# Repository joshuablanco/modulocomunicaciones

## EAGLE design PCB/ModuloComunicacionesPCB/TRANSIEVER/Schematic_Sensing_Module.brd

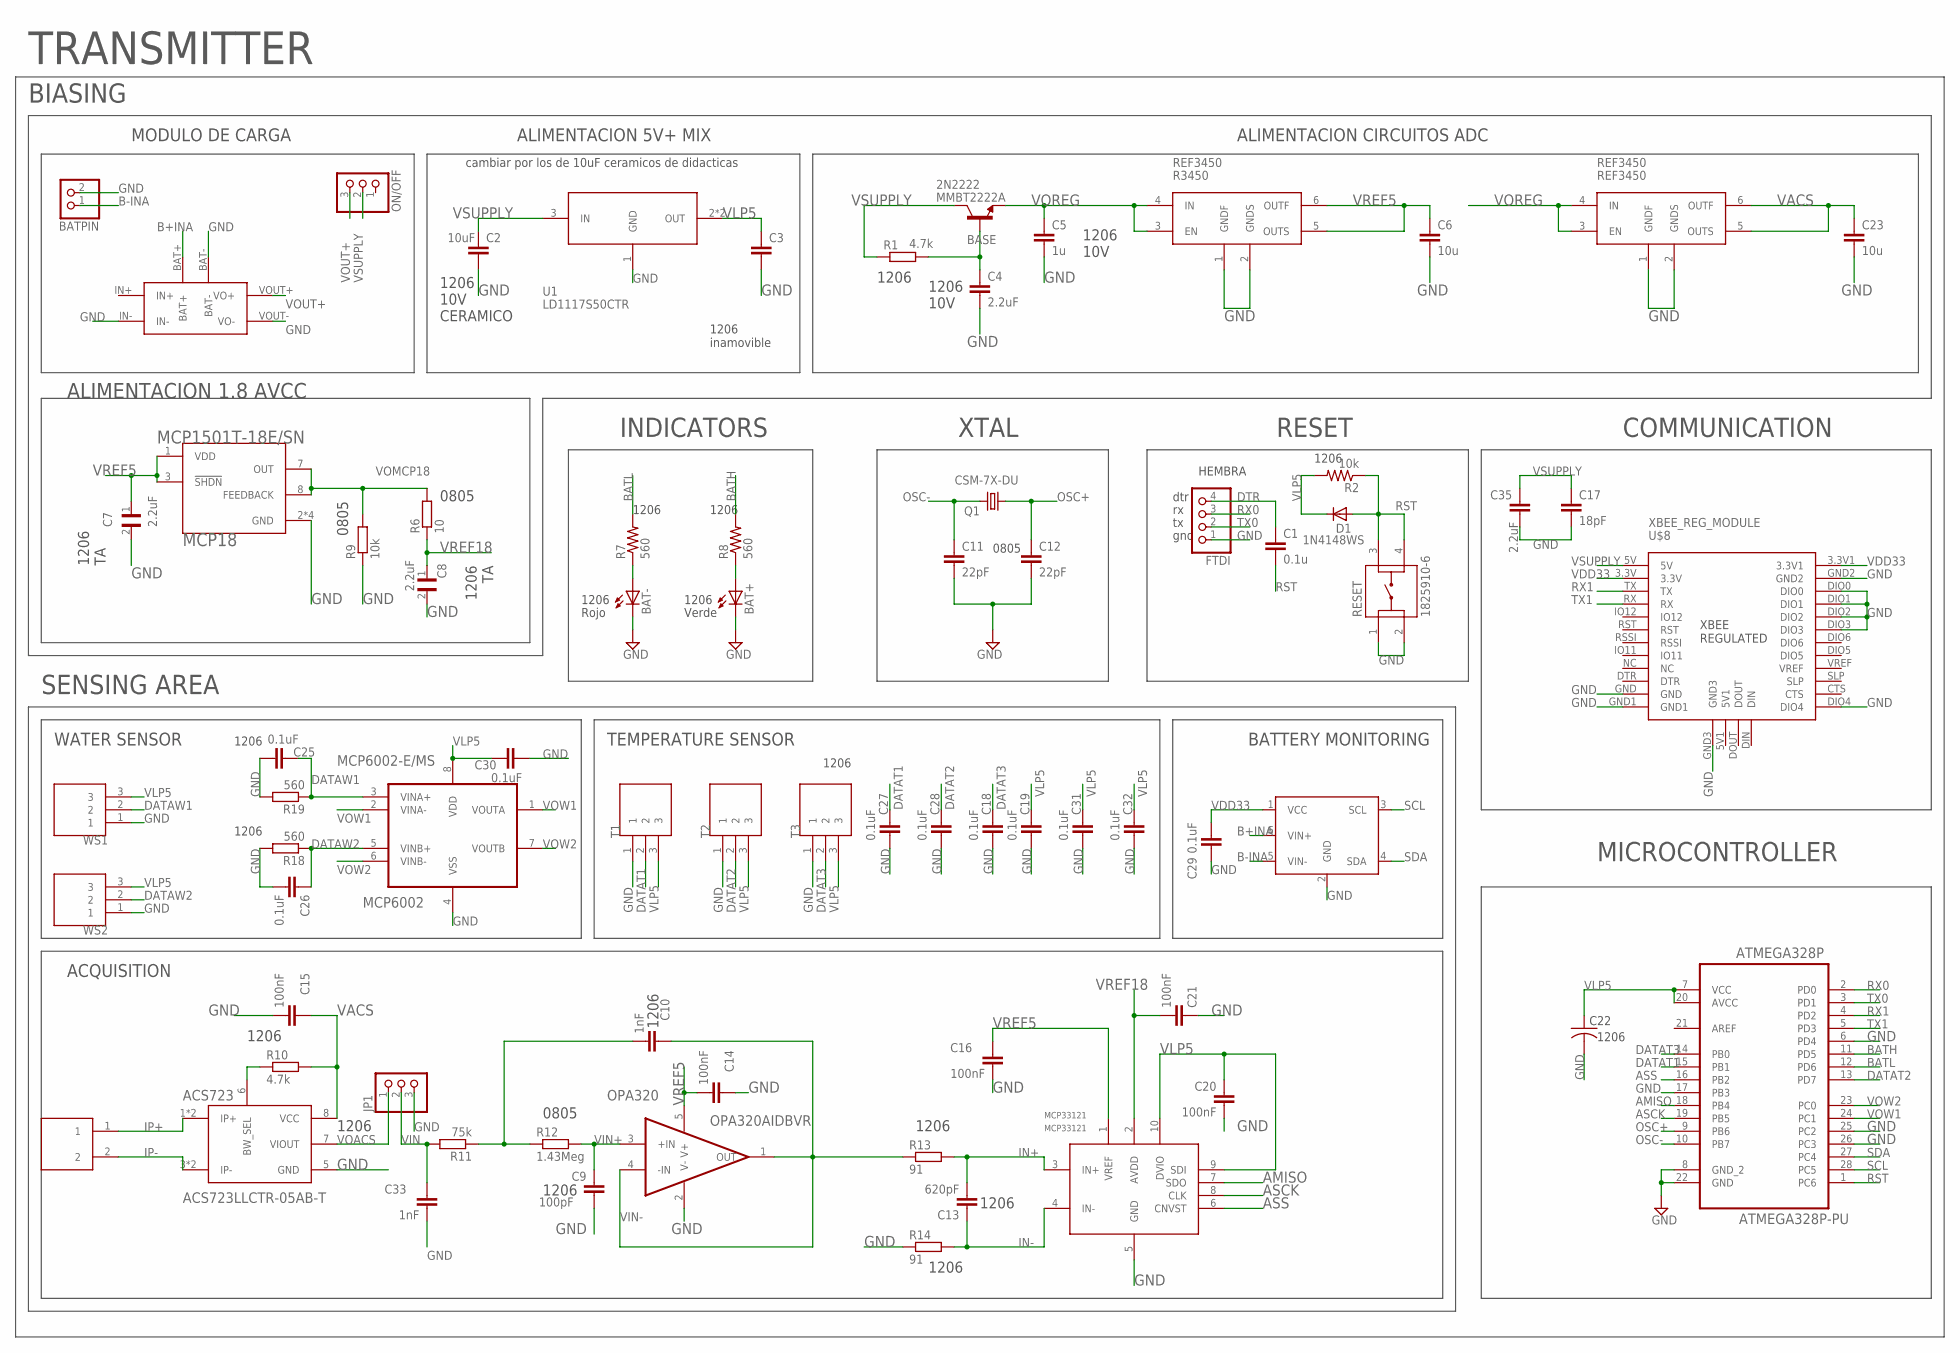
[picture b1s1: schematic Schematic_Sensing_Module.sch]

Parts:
2N2222: MMBT2222A; SOT23
ACS723: ACS723LLCTR-05AB-T; SOIC127P600X175-8N
ATMEGA328P: ATMEGA328P-PU; DIP254P762X457-28
BAT+: LEDCHIPLED_1206; CHIPLED_1206
BAT-: LEDCHIPLED_1206; CHIPLED_1206
BATPIN: PINHD-1X2; 1X02
C1: 0.1u; C0805
C2, C3: 10uF; C1206
C4, C35: 2.2uF; C1206
C5: 1u; C1206
C6, C23: 10u; C1206
C7, C8: 2.2uF; CAPC3216X110N
C9: 100pF; C1206
C10, C33: 1nF; C1206
C11, C12: 22pF; C0805
C13: 620pF; C1206
C14, C15, C16, C20, C21: 100nF; C1206
C17: 18pF; C0805
C18, C19, C22, C25, C26, C27, C28, C29, C30, C31, C32: 0.1uF; C1206
D1: 1N4148WS; SOD323
FTDI: PINHD-1X4; 1X04
IACT: TERMINAL-TB2
INA219: INABB; INA219-MODULE
JP1: PINHD-1X3; 1X03
MCP18: MCP1501T-18E/SN; SOIC127P600X175-8N
MCP6002: MCP6002-E/MS; SOP65P490X110-8N
MCP33121: MCP33121; MSOP10
ON/OFF: PINHD-1X3; 1X03
OPA320: OPA320AIDBVR; SOT95P280X145-5N
POWER-SUPP: MODULO_CARGA_DEVICE; MODULO_CARGA
Q1: CSM-7X-DU
R1: 4.7k; R1206
R2: 10k; R1206
R6: 10; R0805
R7, R8, R18, R19: 560; R1206
R9: 10k; R0805
R10: 4.7k; M1206
R11: 75k; R1206
R12: 1.43Meg; R0805
R13, R14: 91; R1206
R3450: REF3450; SOT95P280X145-6N
REF3450: REF3450; SOT95P280X145-6N
RESET: 1825910-6; SW_1825910-6-4
T1, T2, T3: TERMINAL-TB3
U1: LD1117S50CTR; SOT223
U$8: XBEE_REG_MODULE; XBEE_REG
WS1, WS2: TERMINAL-TB3

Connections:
AMISO: ATMEGA328P.18 (PB4), MCP33121.7 (SDO)
ASCK: ATMEGA328P.19 (PB5), MCP33121.8 (CLK)
ASS: ATMEGA328P.16 (PB2), MCP33121.6 (CNVST)
B+INA: INA219.6 (VIN+), POWER-SUPP.BAT+
B-INA: BATPIN.1, INA219.5 (VIN-)
BASE: 2N2222.1 (B), C4.1, R1.2
BATH: ATMEGA328P.11 (PD5), R8.2
BATL: ATMEGA328P.12 (PD6), R7.2
BWSEL: ACS723.6 (BW_SEL), R10.1
DATAT1: ATMEGA328P.15 (PB1), C27.1, T1.2
DATAT2: ATMEGA328P.13 (PD7), C28.1, T2.2
DATAT3: ATMEGA328P.14 (PB0), C18.1, T3.2
DATAW1: C25.1, MCP6002.3 (VINA+), R19.1, WS1.2
DATAW2: C26.1, MCP6002.5 (VINB+), R18.1, WS2.2
DTR: C1.1, FTDI.4
GND: ACS723.5 (GND), ATMEGA328P.6 (PD4), ATMEGA328P.8 (GND_2), ATMEGA328P.17 (PB3), ATMEGA328P.22 (GND), ATMEGA328P.25 (PC2), ATMEGA328P.26 (PC3), BAT+.C, BAT-.C, BATPIN.2, C2.2, C3.2, C4.2, C5.2, C6.2, C7.2, C8.2, C9.2, C11.2, C12.2, C14.1, C15.2, C16.2, C17.2, C18.2, C19.2, C20.2, C21.1, C22.2, C23.2, C25.2, C26.2, C27.2, C28.2, C29.2, C30.2, C31.2, C32.2, C33.2, C35.2, FTDI.1, INA219.2 (GND), JP1.3, MCP18.2 (GND), MCP18.4 (GND), MCP18.5 (GND), MCP18.6 (GND), MCP6002.4 (VSS), MCP33121.5 (GND), OPA320.2 (V-), POWER-SUPP.BAT-, POWER-SUPP.IN-, POWER-SUPP.VOUT- (VO-), R9.1, R14.1, R18.2, R19.2, R3450.1 (GNDF), R3450.2 (GNDS), REF3450.1 (GNDF), REF3450.2 (GNDS), RESET.1, RESET.2, T1.1, T2.1, T3.1, U1.1 (GND), U$8.DIO0, U$8.DIO1, U$8.DIO2, U$8.DIO3, U$8.DIO4, U$8.GND, U$8.GND1, U$8.GND2, U$8.GND3, WS1.1, WS2.1
IN+: C13.2, MCP33121.3 (IN+), R13.2
IN-: C13.1, MCP33121.4 (IN-), R14.2
IP+: ACS723.1 (IP+), ACS723.2 (IP+), IACT.1
IP-: ACS723.3 (IP-), ACS723.4 (IP-), IACT.2
unnamed: BAT-.A, R7.1
unnamed: BAT+.A, R8.1
unnamed: C10.2, R11.1, R12.1
OSC+: ATMEGA328P.9 (PB6), C12.1, Q1.1
OSC-: ATMEGA328P.10 (PB7), C11.1, Q1.2
RST: ATMEGA328P.1 (PC6), C1.2, D1.A, R2.1, RESET.3, RESET.4
RX0: ATMEGA328P.2 (PD0), FTDI.3
RX1: ATMEGA328P.4 (PD2), U$8.TX
SCL: ATMEGA328P.28 (PC5), INA219.3 (SCL)
SDA: ATMEGA328P.27 (PC4), INA219.4 (SDA)
TX0: ATMEGA328P.3 (PD1), FTDI.2
TX1: ATMEGA328P.5 (PD3), U$8.RX
VACS: ACS723.8 (VCC), C15.1, C23.1, R10.2, REF3450.5 (OUTS), REF3450.6 (OUTF)
VDD33: C29.1, INA219.1 (VCC), U$8.3.3V, U$8.3.3V1
VIN: C33.1, JP1.2, R11.2
VIN+: C9.1, OPA320.3 (+IN), R12.2
VIN-: C10.1, OPA320.1 (OUT), OPA320.4 (-IN), R13.1
VLP5: ATMEGA328P.7 (VCC), ATMEGA328P.20 (AVCC), C3.1, C19.1, C20.1, C22.1, C30.1, C31.1, C32.1, D1.C, MCP6002.8 (VDD), MCP33121.9 (SDI), MCP33121.10 (DVIO), R2.2, T1.3, T2.3, T3.3, U1.2 (OUT), U1.4 (OUT), WS1.3, WS2.3
VOACS: ACS723.7 (VIOUT), JP1.1
VOMCP18: MCP18.7 (OUT), MCP18.8 (FEEDBACK), R6.2, R9.2
VOREG: 2N2222.2 (E), C5.1, R3450.3 (EN), R3450.4 (IN), REF3450.3 (EN), REF3450.4 (IN)
VOUT+: ON/OFF.3, POWER-SUPP.VOUT+ (VO+)
VOW1: ATMEGA328P.24 (PC1), MCP6002.1 (VOUTA), MCP6002.2 (VINA-)
VOW2: ATMEGA328P.23 (PC0), MCP6002.6 (VINB-), MCP6002.7 (VOUTB)
VREF5: C6.1, C7.1, C14.2, C16.1, MCP18.1 (VDD), MCP18.3 (!SHDN), MCP33121.1 (VREF), OPA320.5 (V+), R3450.5 (OUTS), R3450.6 (OUTF)
VREF18: C8.1, C21.2, MCP33121.2 (AVDD), R6.1
VSUPPLY: 2N2222.3 (C), C2.1, C17.1, C35.1, ON/OFF.2, R1.1, U1.3 (IN), U$8.5V

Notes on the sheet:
XTAL
TEMPERATURE SENSOR
WATER SENSOR
RESET
INDICATORS
TRANSMITTER
BATTERY MONITORING
SENSING AREA
BIASING
1206
COMMUNICATION
MICROCONTROLLER
ACQUISITION
Rojo
Verde
HEMBRA
dtr
gnd
MODULO DE CARGA
1206 10V CERAMICO
1206 10V
ALIMENTACION 5V+ MIX
ALIMENTACION CIRCUITOS ADC
0805
1206 TA
ALIMENTACION 1.8 AVCC
1206 inamovible
cambiar por los de 10uF ceramicos de didacticas

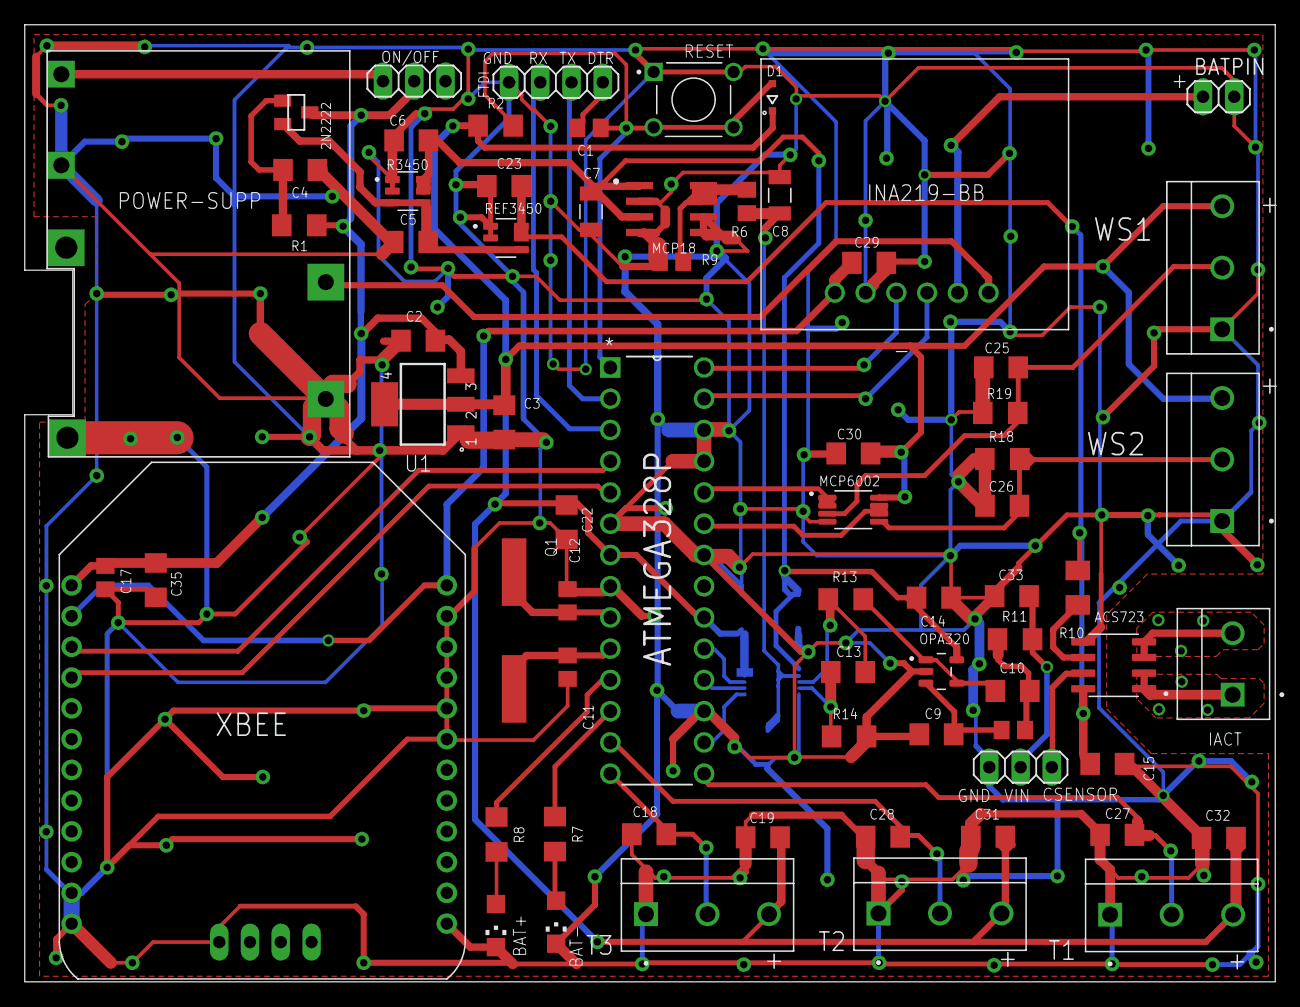
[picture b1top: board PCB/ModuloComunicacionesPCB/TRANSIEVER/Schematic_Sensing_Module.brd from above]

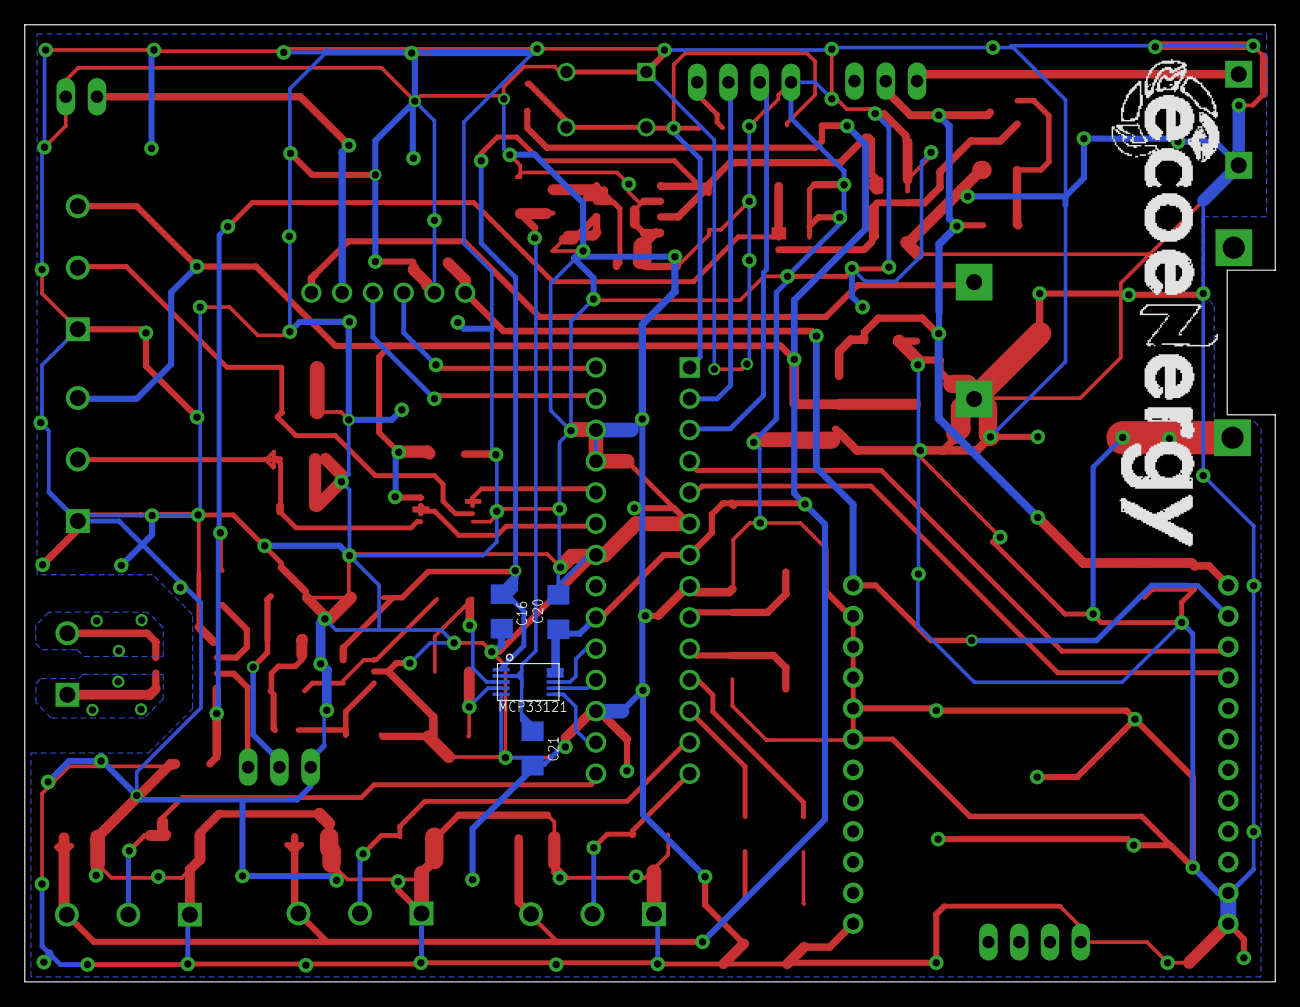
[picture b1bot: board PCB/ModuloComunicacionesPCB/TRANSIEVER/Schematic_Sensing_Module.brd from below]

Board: 2 copper layers, 101.7 x 77.8 mm, 74 parts (4 on the bottom side), 47 nets.

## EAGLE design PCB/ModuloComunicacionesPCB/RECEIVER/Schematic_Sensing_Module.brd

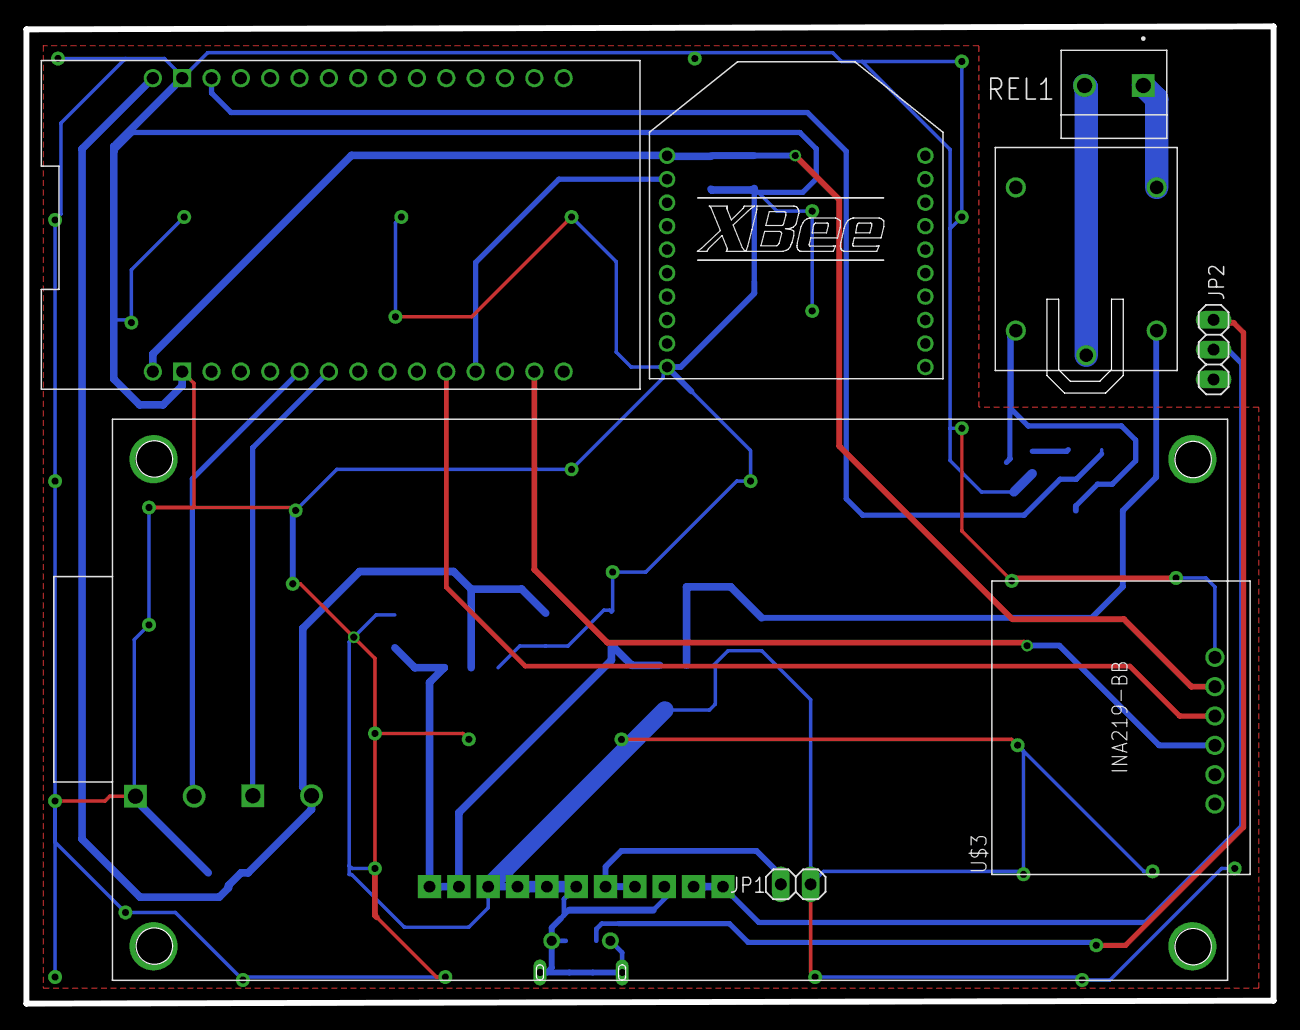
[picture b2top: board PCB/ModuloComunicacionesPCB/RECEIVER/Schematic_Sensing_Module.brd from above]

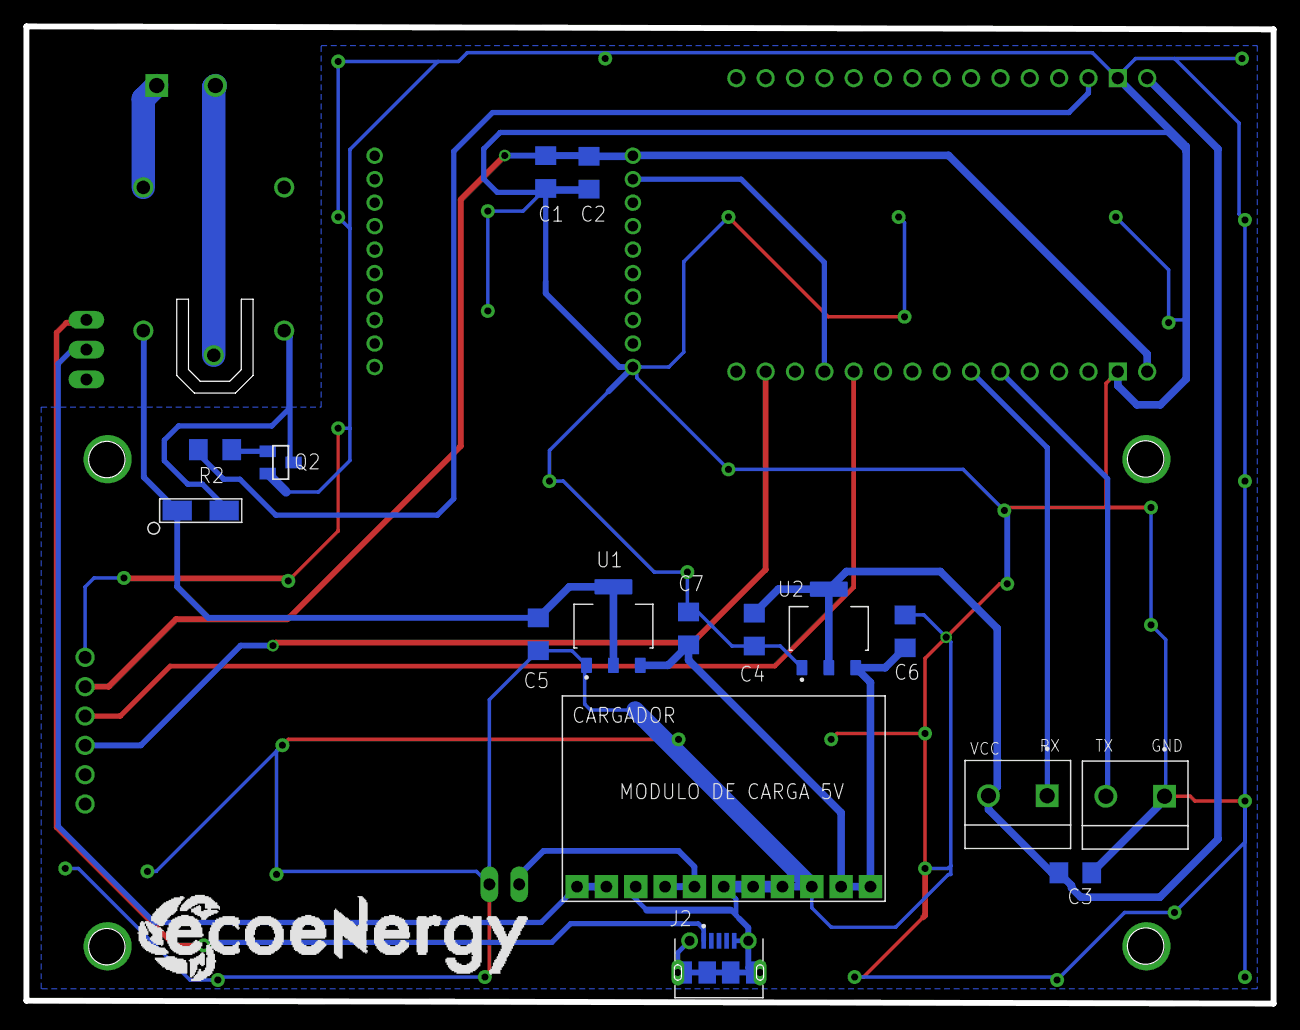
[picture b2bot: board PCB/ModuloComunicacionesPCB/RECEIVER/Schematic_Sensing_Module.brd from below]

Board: 2 copper layers, 106.2 x 83.2 mm, 24 parts (16 on the bottom side), 18 nets.

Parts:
1N4007: 1N4007SMA; SMA
C1, C3: 100nF; C1206
C2: 1u; C1206
C4, C5, C6, C7: C1206
CARGADOR: MODULO_CARGA_5V
CONN1, CONN2: TERMINAL-TB2
J2: 1050170001; MOLEX_1050170001
JP1: 1X02
JP2: 1X03
Q2: MMBT2222A; SOT23
R2: 10k; R1206
REL1: TERMINAL-TB2
U1, U2: AMS1117-5.0; SOT229P700X180-4N
U$1: ESP32-W; DIP
U$2: NX4024T032
U$3: INABB; INA219-MODULE
U$5: SRD-3; SRD-N
U$9: XBEE-S2C; XBEE-DIP

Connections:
CR1: REL1.2, U$5.C
DOUT: U$1.RX0, U$9.2
GND: C1.2, C2.1, C3.2, C4.2, C5.2, C6.2, C7.2, CARGADOR.GND, CARGADOR.GND1, CARGADOR.GND2, CARGADOR.GND3, CARGADOR.GND4, CONN1.1, J2.5, J2.SH1, J2.SH2, J2.SH3, J2.SH4, J2.SH5, J2.SH6, J2.SH7, J2.SH8, JP1.2, Q2.2, U1.1, U2.1, U$1.GND, U$1.GND1, U$3.6, U$9.10
unnamed: Q2.1, R2.2
unnamed: 1N4007.1, Q2.3, U$5.VL-
NOR1: REL1.1, U$5.NO
RXNEX: CONN2.1, U$1.TX2
SCL: U$1.D22, U$3.3
SDA: U$1.D21, U$3.4
TXNEX: CONN1.2, U$1.RX2
VBAT: CARGADOR.BAT, CARGADOR.BAT1, JP1.1
VDEVICES: C3.1, C4.1, CONN2.2, U2.2, U2.4, U$1.VIN
VINCHAR: J2.1, JP2.1
VON: CARGADOR.VIN, CARGADOR.VIN1, JP2.2
VOUTCH: C6.1, C7.1, CARGADOR.VOUT, CARGADOR.VOUT1, U1.3, U2.3
VOUTRELAYS: 1N4007.2, C5.1, U1.2, U1.4, U$5.VL+
VR1: R2.1, U$1.D13
VXBEE: C1.1, C2.2, U$1.3V3, U$3.5, U$9.1

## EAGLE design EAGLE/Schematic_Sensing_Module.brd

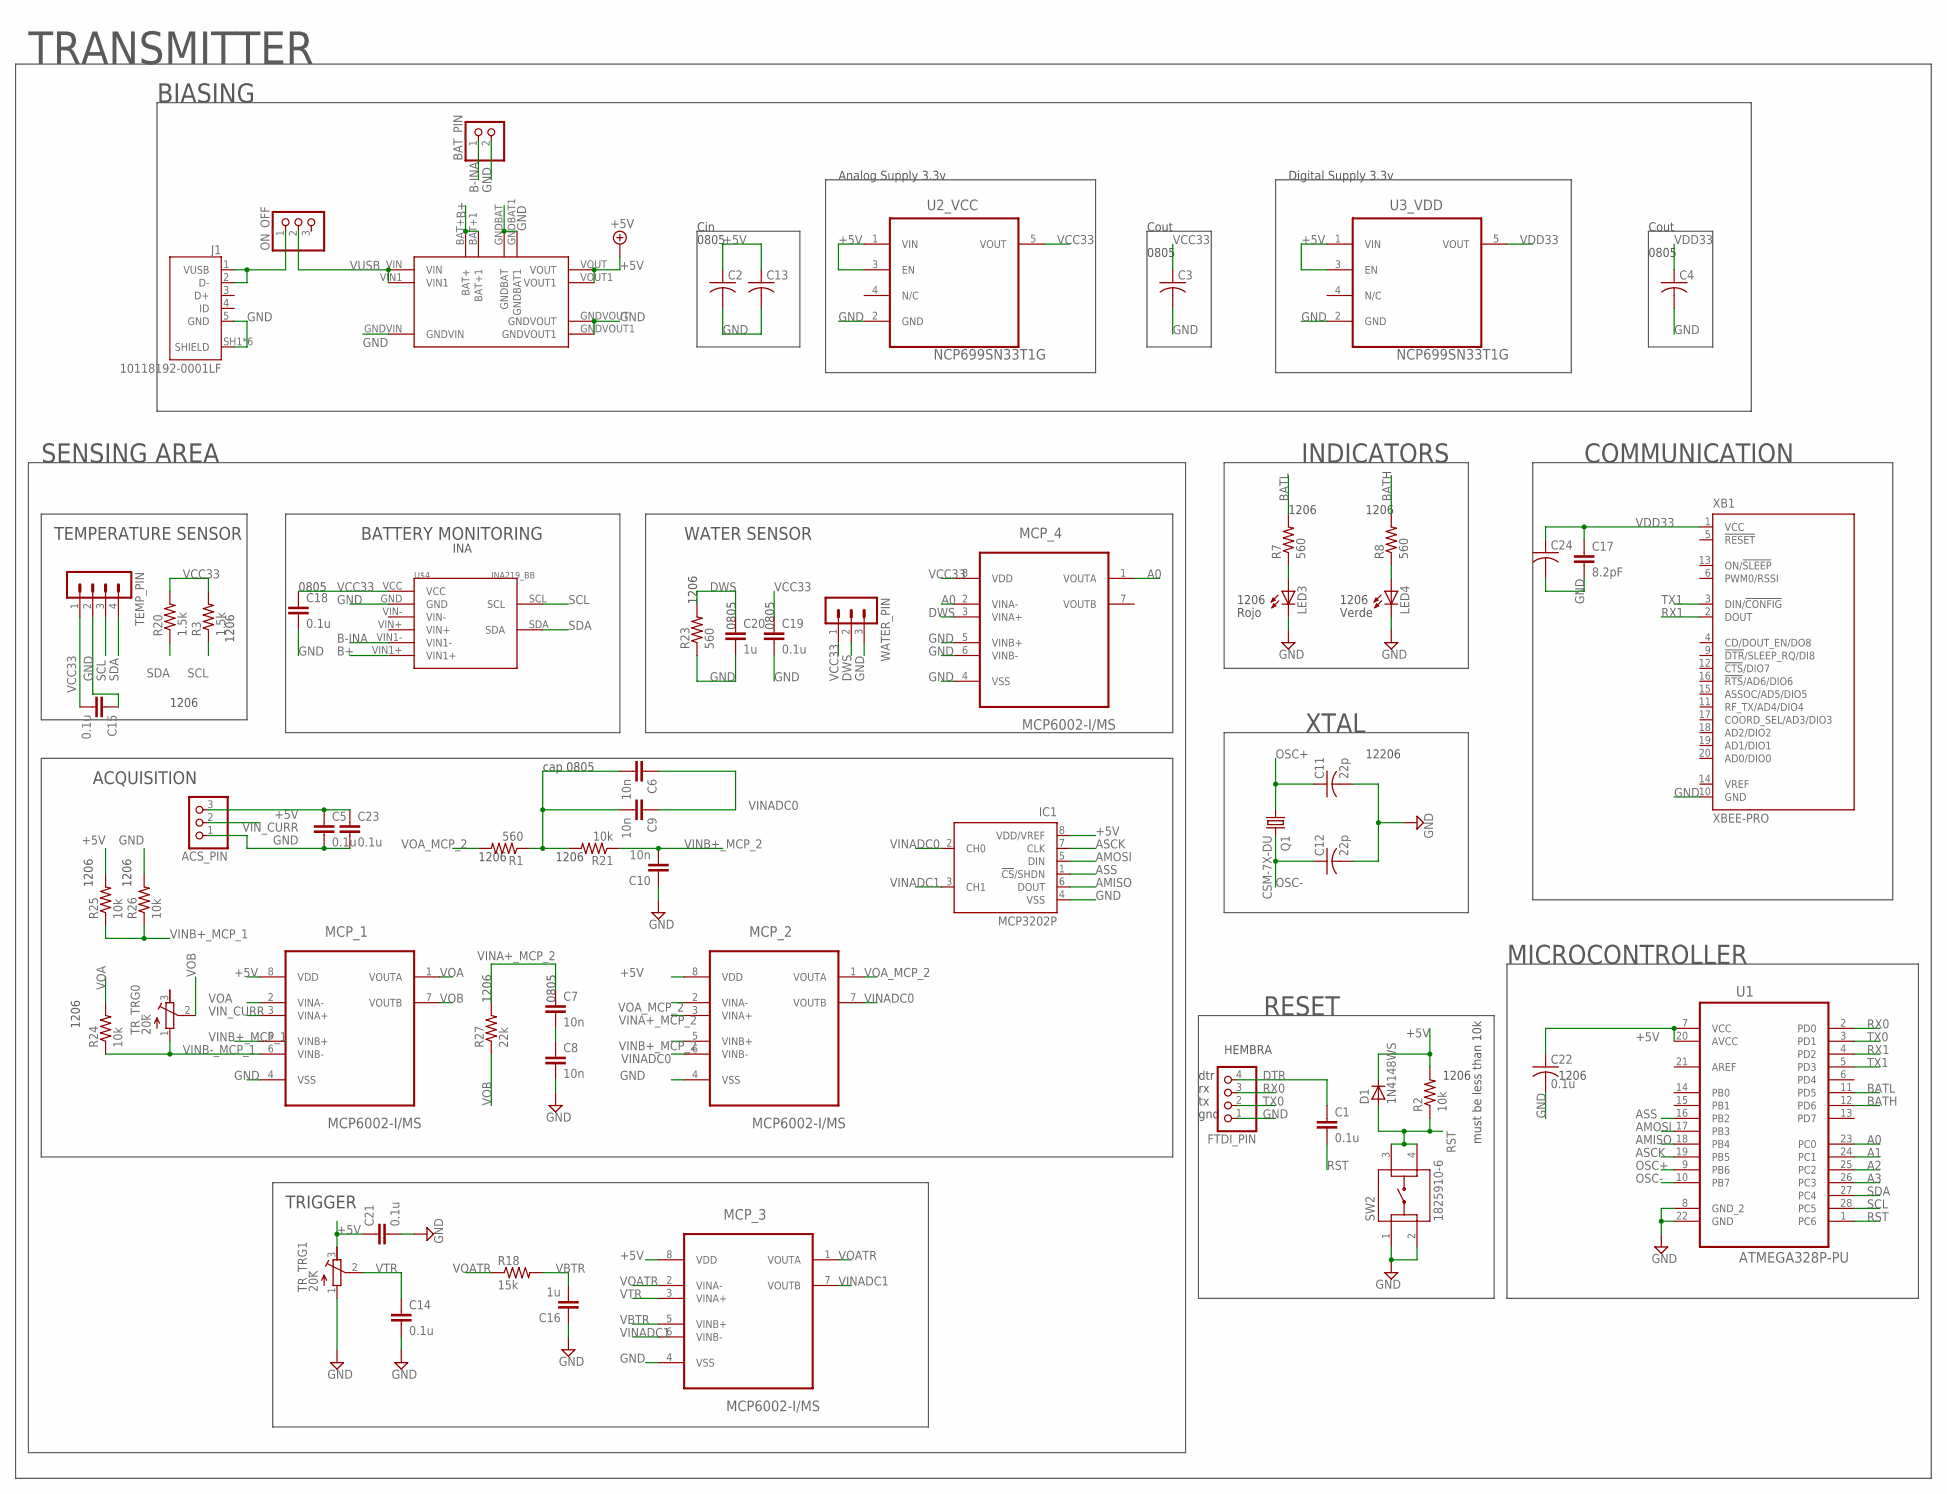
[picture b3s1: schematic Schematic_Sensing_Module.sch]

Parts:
ACS_PIN: PINHD-1X3; 1X03
BAT_PIN: PINHD-1X2; 1X02
C1, C5, C14, C15, C18, C19, C21, C23: 0.1u; C0805
C2, C3, C4, C13, C24: C-USC0805; C0805
C6, C7, C8, C9, C10: 10n; C0805
C11, C12: 22p; C1206
C16, C20: 1u; C0805
C17: 8.2pF; C0805
C22: 0.1u; C1206
D1: 1N4148WS; SOD323
FTDI_PIN: PINHD-1X4; 1X04
IC1: MCP3202P; DIL8
J1: 10118192-0001LF; AMPHENOL_10118192-0001LF
LED3, LED4: LEDCHIPLED_1206; CHIPLED_1206
MCP_1, MCP_2, MCP_3, MCP_4: MCP6002-I/MS; SOP65P490X110-8N
ON_OFF: PINHD-1X3; 1X03
Q1: CSM-7X-DU
R1, R7, R8, R23: 560; R1206
R2, R21, R24, R25, R26: 10k; R1206
R3, R20: 1.5k; R1206
R18: 15k; R0805
R27: 22k; R1206
SW2: 1825910-6; SW_1825910-6-4
TEMP_PIN: MA04-1
TR_TRG0: 20k; RTRIM64W
TR_TRG1: 20K; RTRIM64W
U1: ATMEGA328P-PU; DIP254P762X457-28
U2_VCC, U3_VDD: NCP699SN33T1G; SOT95P275X110-5N
U$2: UPS-LIPO
U$4: INA219_BB
WATER_PIN: MA03-1
XB1: XBEE-PRO

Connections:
+5V: ACS_PIN.3, C2.1, C5.1, C13.1, C21.1, C22.1, C23.1, D1.C, IC1.8 (VDD/VREF), MCP_1.8 (VDD), MCP_2.8 (VDD), MCP_3.8 (VDD), R2.2, R25.2, TR_TRG1.3 (E), U1.7 (VCC), U1.20 (AVCC), U2_VCC.1 (VIN), U2_VCC.3 (EN), U3_VDD.1 (VIN), U3_VDD.3 (EN), U$2.VOUT, U$2.VOUT1
A0: MCP_4.1 (VOUTA), MCP_4.2 (VINA-), U1.23 (PC0)
A1: U1.24 (PC1)
A2: U1.25 (PC2)
A3: U1.26 (PC3)
AMISO: IC1.6 (DOUT), U1.18 (PB4)
AMOSI: IC1.5 (DIN), U1.17 (PB3)
ASCK: IC1.7 (CLK), U1.19 (PB5)
ASS: IC1.1 (!CS!/SHDN), U1.16 (PB2)
B+: U$2.BAT+, U$2.BAT+1, U$4.VIN1+
B-INA: BAT_PIN.1, U$4.VIN1-
BATH: R8.2, U1.12 (PD6)
BATL: R7.2, U1.11 (PD5)
DTR: C1.1, FTDI_PIN.4
DWS: C20.1, MCP_4.3 (VINA+), R23.2, WATER_PIN.2
GND: ACS_PIN.1, BAT_PIN.2, C2.2, C3.2, C4.2, C5.2, C8.2, C10.1, C11.2, C12.2, C13.2, C14.2, C15.1, C16.1, C17.2, C18.2, C19.2, C20.2, C21.2, C22.2, C23.2, C24.2, FTDI_PIN.1, IC1.4 (VSS), J1.5 (GND), J1.SH1 (SHIELD), J1.SH2 (SHIELD), J1.SH3 (SHIELD), J1.SH4 (SHIELD), J1.SH5 (SHIELD), J1.SH6 (SHIELD), LED3.C, LED4.C, MCP_1.4 (VSS), MCP_2.4 (VSS), MCP_3.4 (VSS), MCP_4.4 (VSS), MCP_4.5 (VINB+), MCP_4.6 (VINB-), R23.1, R26.2, SW2.1, SW2.2, TEMP_PIN.2, TR_TRG1.1 (A), U1.8 (GND_2), U1.22 (GND), U2_VCC.2 (GND), U3_VDD.2 (GND), U$2.GNDBAT, U$2.GNDBAT1, U$2.GNDVIN, U$2.GNDVOUT, U$2.GNDVOUT1, U$4.GND, WATER_PIN.3, XB1.10 (GND)
unnamed: J1.1 (VUSB), J1.2 (D-), ON_OFF.1
unnamed: LED3.A, R7.1
unnamed: LED4.A, R8.1
unnamed: C7.2, C8.1
unnamed: C6.2, C9.2, R1.1, R21.2
OSC+: C11.1, Q1.1, U1.9 (PB6)
OSC-: C12.1, Q1.2, U1.10 (PB7)
RST: C1.2, D1.A, R2.1, SW2.3, SW2.4, U1.1 (PC6)
RX0: FTDI_PIN.3, U1.2 (PD0)
RX1: U1.4 (PD2), XB1.2 (DOUT)
SCL: R3.1, TEMP_PIN.3, U1.28 (PC5), U$4.SCL
SDA: R20.1, TEMP_PIN.4, U1.27 (PC4), U$4.SDA
TX0: FTDI_PIN.2, U1.3 (PD1)
TX1: U1.5 (PD3), XB1.3 (DIN/!CONFIG)
VBTR: C16.2, MCP_3.5 (VINB+), R18.2
VCC33: C3.1, C15.2, C18.1, C19.1, MCP_4.8 (VDD), R3.2, R20.2, TEMP_PIN.1, U2_VCC.5 (VOUT), U$4.VCC, WATER_PIN.1
VDD33: C4.1, C17.1, C24.1, U3_VDD.5 (VOUT), XB1.1 (VCC)
VINA+_MCP_2: C7.1, MCP_2.3 (VINA+), R27.2
VINADC0: C6.1, C9.1, IC1.2 (CH0), MCP_2.6 (VINB-), MCP_2.7 (VOUTB)
VINADC1: IC1.3 (CH1), MCP_3.6 (VINB-), MCP_3.7 (VOUTB)
VINB+_MCP_1: MCP_1.5 (VINB+), R25.1, R26.1
VINB+_MCP_2: C10.2, MCP_2.5 (VINB+), R21.1
VINB-_MCP_1: MCP_1.6 (VINB-), R24.1, TR_TRG0.1 (A)
VIN_CURR: ACS_PIN.2, MCP_1.3 (VINA+)
VOA: MCP_1.1 (VOUTA), MCP_1.2 (VINA-), R24.2
VOATR: MCP_3.1 (VOUTA), MCP_3.2 (VINA-), R18.1
VOA_MCP_2: MCP_2.1 (VOUTA), MCP_2.2 (VINA-), R1.2
VOB: MCP_1.7 (VOUTB), R27.1, TR_TRG0.2 (S)
VTR: C14.1, MCP_3.3 (VINA+), TR_TRG1.2 (S)
VUSB: ON_OFF.2, U$2.VIN, U$2.VIN1

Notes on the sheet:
XTAL
TEMPERATURE SENSOR
WATER SENSOR
RESET
INDICATORS
TRANSMITTER
BATTERY MONITORING
SENSING AREA
BIASING
1206
12206
COMMUNICATION
MICROCONTROLLER
ACQUISITION
cap 0805
TRIGGER
must be less than 10k
Cin
Cout
Analog Supply 3.3v
Digital Supply 3.3v
0805
Rojo
Verde
INA
HEMBRA
dtr
gnd

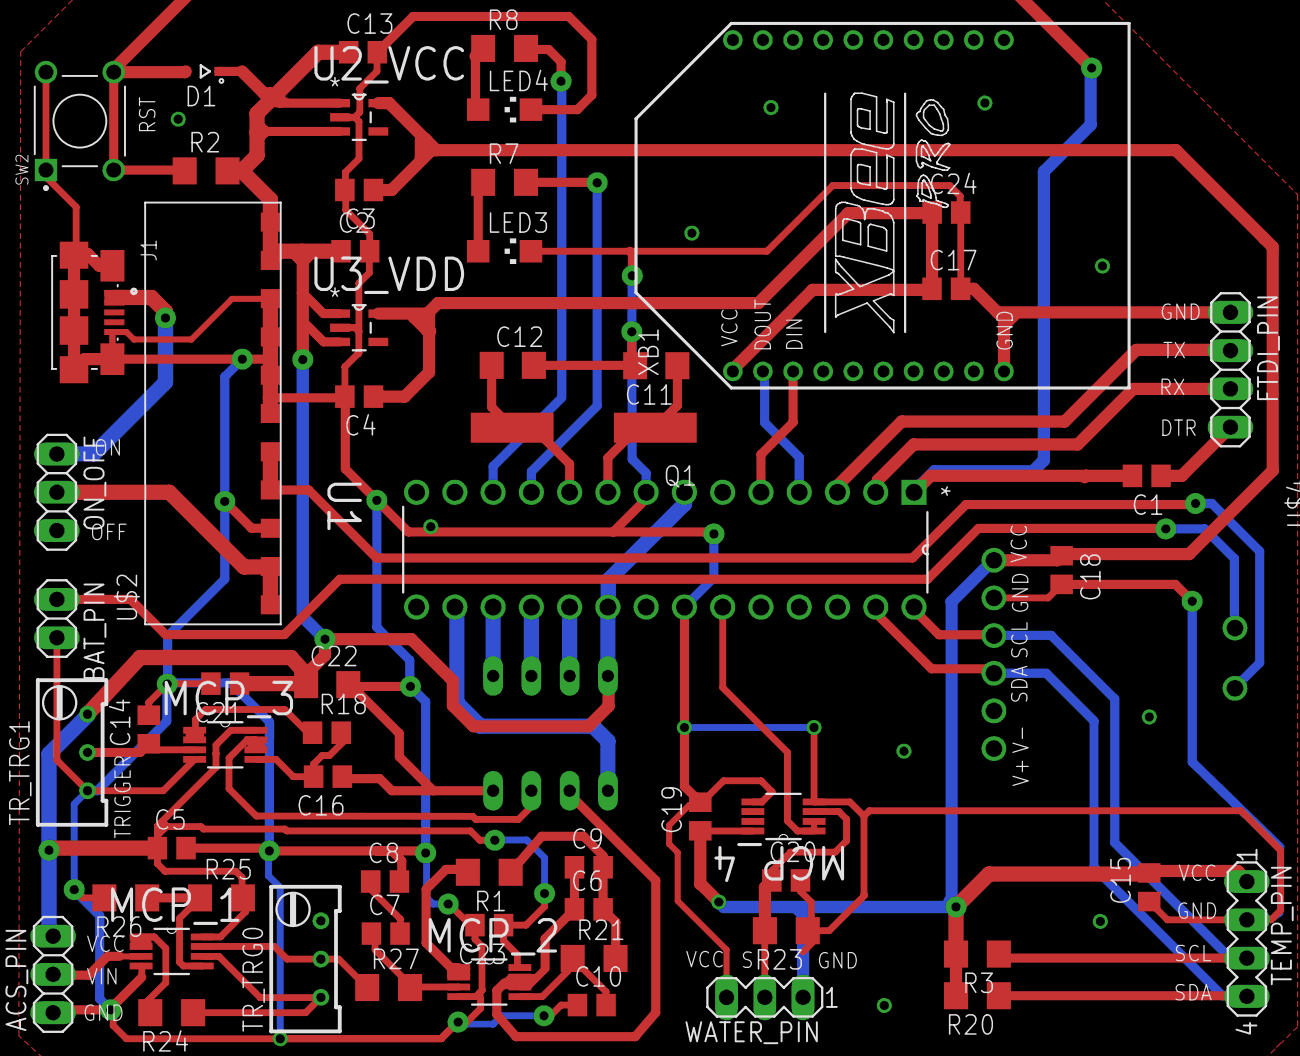
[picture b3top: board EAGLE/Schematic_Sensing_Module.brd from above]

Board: 2 copper layers, 62 parts (1 on the bottom side), 43 nets.

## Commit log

2021-01-08 commit antes de meter la carpeta de documentos
2021-01-08 editando router para hacer librerias convirtiendo archivos a header
2021-01-09 WaterRead library
2021-01-09 hechura de TempHum.lib la cual lee con dht22new y genera las variables de interes
2021-01-09 correccion de comentario en header
2021-01-09 no matter commit
2021-01-09 erasing folders of libraries unuseful
2021-01-10 Changed of Water header to WR
2021-01-11 fixing temperature and water .ino file[
2021-01-11 commit unuseful
2021-01-11 erasing digikey print
2021-01-11 commit but not working the Grafica.ino doesnt recognize the function in void loop()
2021-01-13 echura de libreria
2021-01-13 terminacion router
2021-01-15 empezando con la pcb realizacion de componentes de la pcb y sacando el inventario
2021-01-15 adding inventario
2021-01-22 adicion de excel de componentes algunas librerias de reguladores en eagle adicion de multiplicador de cap, mod de codigo
2021-01-25 avance en esquematico para la PCB
2021-01-26 terminacion de esquematico e inicio del esquematico del coordinador
2021-01-30 avances en placing de la pcb del transmisor
2021-01-31 placing almost done
2021-01-31 Finished Placing-Give a review
2021-02-05 pcb ruteada falta plano de tierra
2021-02-06 modelado 3D terminado falta plano de tierra
2021-02-06 adding lib eagle
2021-02-09 ajustando tierra
2021-02-09 transmisor terminado
2021-02-10 receiver placing
2021-02-11 screen ino verified screen and placing in receiving corrected
2021-02-17 pcb enviadas a produccion
2021-02-17 commit dummy
2021-02-17 correccion Router v1.0.2
2021-03-01 edicion de codigo para energia solamente... pruebas
2021-04-20 pequeno avance
2021-04-29 pequeños avances en el libro
2021-05-13 avances
2021-06-26 advances in my book
